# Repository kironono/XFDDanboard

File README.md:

XFD Danboard
=============

``XFD Danboard`` is a XFD (eXtreme Feedback Device).

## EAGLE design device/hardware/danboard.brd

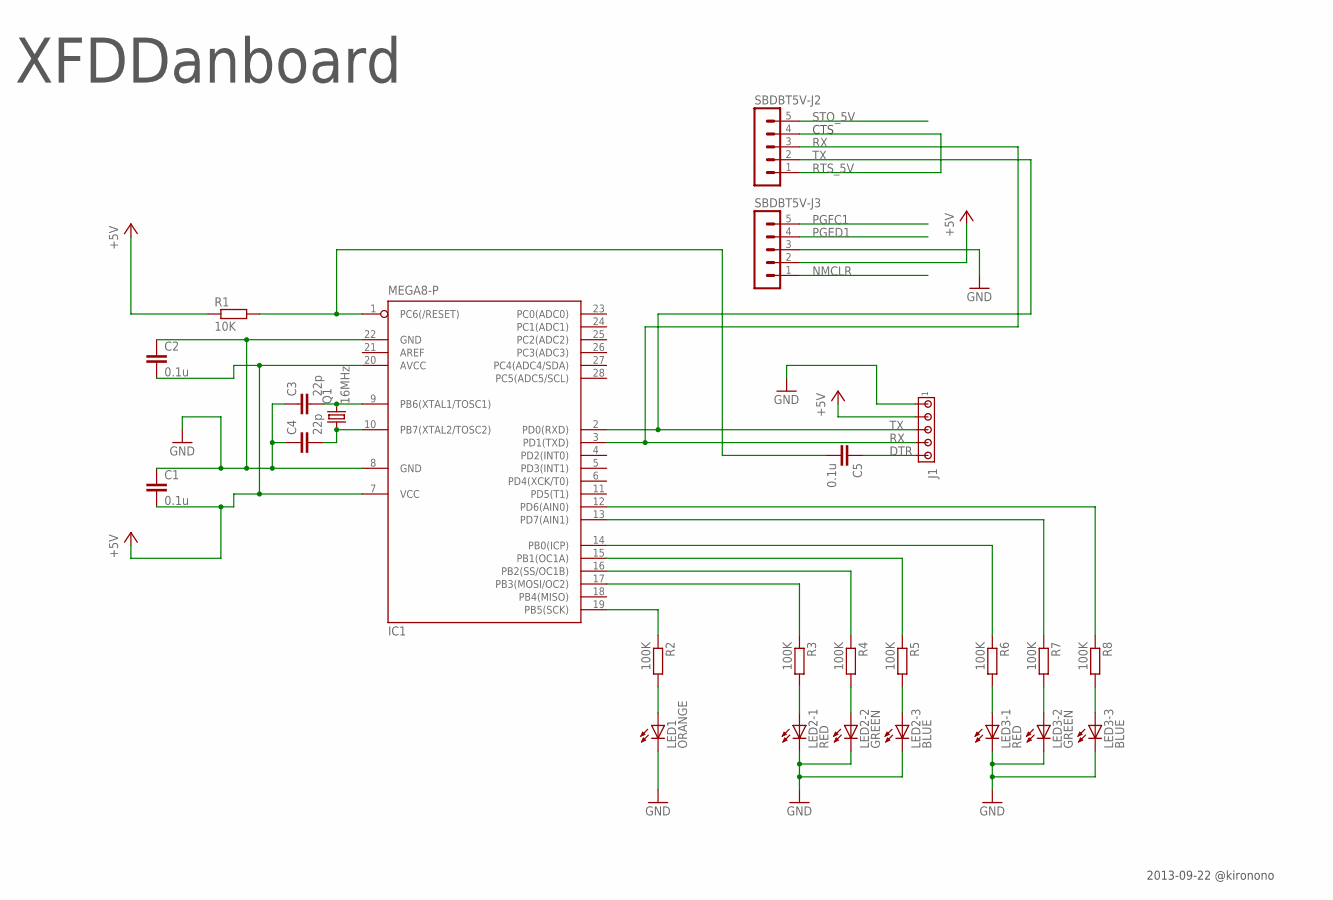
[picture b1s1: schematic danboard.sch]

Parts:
C1, C2, C5: 0.1u; C025-024X044
C3, C4: 22p; C025-024X044
IC1: MEGA8-P; DIL28-3
J1: MTA05-100; 10X05MTA
LED1: ORANGE; LED3MM
LED2-1, LED3-1: RED; LED3MM
LED2-2, LED3-2: GREEN; LED3MM
LED2-3, LED3-3: BLUE; LED3MM
Q1: 16MHz; HC49/S
R1: 10K; 0204/5
R2, R3, R4, R5, R6, R7, R8: 100K; 0204/5
SBDBT5V-J2, SBDBT5V-J3: MA05-1

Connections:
+5V: C1.2, C2.2, IC1.7 (VCC), IC1.20 (AVCC), J1.2, R1.1, SBDBT5V-J3.2
DTR: C5.2, IC1.1 (PC6(/RESET)), R1.2
GND: C1.1, C2.1, C3.1, C4.1, IC1.8 (GND), IC1.22 (GND), J1.1, LED1.K (C), LED2-1.K (C), LED2-2.K (C), LED2-3.K (C), LED3-1.K (C), LED3-2.K (C), LED3-3.K (C), SBDBT5V-J3.3
unnamed: IC1.14 (PB0(ICP)), R6.1
unnamed: C3.2, IC1.9 (PB6(XTAL1/TOSC1)), Q1.2
unnamed: C4.2, IC1.10 (PB7(XTAL2/TOSC2)), Q1.1
unnamed: IC1.19 (PB5(SCK)), R2.1
unnamed: LED1.A, R2.2
unnamed: IC1.13 (PD7(AIN1)), R7.1
unnamed: LED2-1.A, R3.2
unnamed: C5.1, J1.5
unnamed: LED2-2.A, R4.2
unnamed: LED2-3.A, R5.2
unnamed: LED3-1.A, R6.2
unnamed: LED3-2.A, R7.2
unnamed: LED3-3.A, R8.2
unnamed: IC1.12 (PD6(AIN0)), R8.1
unnamed: IC1.17 (PB3(MOSI/OC2)), R3.1
unnamed: IC1.16 (PB2(SS/OC1B)), R4.1
unnamed: IC1.15 (PB1(OC1A)), R5.1
NMCLR: SBDBT5V-J3.1
PGED1: SBDBT5V-J3.4
PGFC1: SBDBT5V-J3.5
RTS_5V: SBDBT5V-J2.1, SBDBT5V-J2.4
RX: J1.4, SBDBT5V-J2.3
STO_5V: SBDBT5V-J2.5
TX: J1.3, SBDBT5V-J2.2

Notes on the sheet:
XFDDanboard
CTS
2013-09-22 @kironono

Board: 2 copper layers, 25 parts (0 on the bottom side), 23 nets, no tracks yet.

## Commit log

2013-09-10 init.
2013-09-10 update README.
2013-09-23 eagle プロジェクトを追加
2013-10-24 Create gh-pages branch via GitHub
